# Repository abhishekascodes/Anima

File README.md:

# ANIMA: Interactive Tabletop Rock-Paper-Scissors Robot

Hey! I am Abhishek, and this is **ANIMA**, an interactive humanoid tabletop robot designed to play Rock-Paper-Scissors with people in real time. I am building this project for **Hack Club Fallen** with the goal of bringing it to showcase at **Maker Faire Shenzhen 2026**.

---

## The Backstory (Or how I almost built an uncontrollable monster)

When I first started this project, I went down a crazy rabbit hole trying to build a 51-axis radial sphere organism. I thought having 48 micro servos wiggling in a giant ball would look incredible. 

It did not. 

Once I actually modeled it and ran the mechanical load numbers, reality hit me pretty hard:
1. **The power draw was absurd:** 48 servos running under load would pull upwards of 50 to 60 amps at stall. Trying to route that through moving joints is an easy way to start an electrical fire on a table.
2. **The physics did not work:** The moment arms on the radial links put massive cantilever bending torque right onto tiny plastic servo splines. They would have stripped in ten minutes.
3. **It was not fun to interact with:** At the end of the day, it was just a mechanical ball wiggling on a pole. People at a booth would look at it for five seconds and walk away.

So I scrapped the entire thing and pivoted to something I actually care about: a robot with personality that people can walk up to, play against, and laugh with. That is where ANIMA was born.

---

## Why Rock-Paper-Scissors? (And the Anti-Cheat Problem)

Almost every Rock-Paper-Scissors robot you see on YouTube or in research labs has a dirty secret: **it cheats**. 

They mount a 120 FPS high-speed camera pointed at your hand, run a lightweight computer vision model that detects the first 20 milliseconds of your fingers unfolding, and snap their winning move right before you finish throwing. You feel like the robot has superhuman reflexes, but really it is just waiting for you to commit and picking the counter.

I wanted ANIMA to play like a real human, with genuine stakes and proof that it is not looking at your hand:

* **Pre-Commitment:** Before the countdown even starts, the host computer picks its move randomly, hashes it with a 24-byte secret key using SHA-256, and splashes the hash across the big screen.
* **Physical Blackout:** While the countdown is running, a micro servo swings a physical, opaque blackout shutter blade over the camera lens. The robot literally cannot see you.
* **Instant Mechanical Throw:** On the final beat, high-speed electromagnetic solenoids yank Kevlar tendons to snap the fingers into Rock, Paper, or Scissors in under 15 milliseconds.
* **Cryptographic Reveal:** Digital Hall effect sensors at the finger stops verify that the hand physically reached the pose. Only after the physical throw is locked does the camera shutter swing open, the secret key get published, and the winner get called. Anyone watching can verify the hash matches the pre-countdown commitment.

---

## Visual Showcase

| Hero Striker Angle | Expressive Portrait View |
| :---: | :---: |
|  |  |

| Internal Cutaway & Tendon Routing | High-Speed Playing Hand |
| :---: | :---: |
|  |  |

| Custom 4-Layer Controller (KiCad 10) | Multi-Sheet Schematic |
| :---: | :---: |
|  |  |

---

## How It Works Under the Hood

### 1. Mechanics and 3D Printed Parts
I split the 3D design into two layers:
* **The structural skeleton (`cad/Parts/` and `ANIMA_RPS_Upper_Torso.FCStd`):** Modeled with exact engineering tolerances in FreeCAD and CadQuery. Every joint that experiences side loads (like the neck pan and striker arm) rides on 688ZZ radial ball bearings so the motor shafts never take bending stress. Brass M3 heat-set inserts are melted into every mounting boss so you can disassemble and rebuild it without stripping plastic threads.
* **The sculpted outer shell (`cad/ANIMA Studio.blend` and `.glb`):** Modeled in Blender to give ANIMA a friendly, retro-futuristic aesthetic. The outer shells cover all the ugly wire harnesses while leaving airflow ducts for the heatsinks and solenoids.

For the fingers, standard servos were way too slow (they take 100 to 200 ms to rotate 60 degrees). Instead, I used **12V pull solenoids** attached to braided 100 lb Dyneema/Kevlar lines running through low-friction PTFE guide tubes. When a coil fires, the fingers snap shut in about 12 to 15 ms, fast enough to match human reflex speed.

### 2. Custom 4-Layer PCB (`ANIMA_RPS_Controller`)
You cannot run high-current inductive solenoids off breadboards or standard hobby shields without crashing your microcontroller. Every time a solenoid coil turns off, the collapsing magnetic field throws a massive negative voltage spike that resets the CPU.

To solve this, I designed a dedicated 4-layer PCB in KiCad 10:
* **Brain:** ESP32-S3-WROOM-1 module running hardware PWM timers and fast GPIO pin-change interrupts for the Hall effect limit sensors.
* **Power Isolation:** The 3.3V digital logic has its own ground plane and is powered through an onboard AP63203 buck converter. The 12V coil rail is completely separated, driven by fast UCC27517 gate drivers, IRLZ44N power MOSFETs, SS54 Schottky catch diodes, and SMBJ24A TVS diodes to soak up inductive kickback.
* **Safety Hardware:** A physical emergency stop button runs straight into an onboard SN74LVC1G00 hardware logic gate. If someone hits the E-stop, the power to all coils and servos is killed in hardware immediately, even if the microcontroller firmware locks up.
* **Audio & Presence:** An onboard MAX98357A I2S Class-D amplifier drives an internal speaker for voice lines and sound effects, and an LD2410 24 GHz mmWave radar header detects when someone walks up to the booth.

### 3. Firmware and Software Architecture
* **ESP32-S3 Firmware (`firmware/esp32/`):** Written in C++ using PlatformIO. Uses high-resolution hardware timers (LEDC) to command servos with zero jitter. When a move is triggered, it pulses the solenoid MOSFETs with an initial 100% kick for 25 ms to overcome mechanical inertia, then drops to a 30% PWM hold current so the coils do not overheat.
* **Host Vision & Game Engine (`firmware/pi/`):** Runs on a Raspberry Pi 5. It handles MediaPipe hand tracking for visitor gesture recognition, manages game state, drives the HDMI commitment display, and communicates with the ESP32 over high-speed USB-serial at 921,600 baud.

---

## Repository Tour

Here is what you will find in this repo:

```
├── cad/
│   ├── README.md                     # Joint angles, mechanical specs and print settings
│   ├── ANIMA Studio.blend            # Master Blender model for outer shells and renders
│   ├── ANIMA Studio.glb              # 3D web asset you can view in your browser
│   ├── ANIMA Studio Fairing Envelopes.step # Clean exterior CAD surfaces
│   ├── ANIMA_RPS_Upper_Torso.FCStd   # Parametric FreeCAD assembly
│   ├── ANIMA_RPS_Upper_Torso.step    # Full structural assembly STEP
│   ├── anima_rps_assembly.py         # Python CadQuery script generating the skeleton
│   └── Parts/                        # All 41 individual 3D printable leaf parts
├── electronics/
│   ├── ANIMA_RPS_Controller.kicad_sch # Complete 8-sheet KiCad schematic (0 ERC errors)
│   ├── ANIMA_RPS_Controller.kicad_pcb # Routed 4-layer PCB layout (0 DRC errors)
│   ├── gerbers.zip                   # Ready-to-order fab package for JLCPCB / PCBWay
│   └── PCB_BOM.csv                   # Part numbers and footprints for all 47 components
├── firmware/
│   ├── esp32/                        # PlatformIO C++ firmware with hardware timers
│   └── pi/                           # Python host scripts and FAIR anti-cheat demo
├── docs/
│   ├── FAIR_PROTOCOL.md              # Deep dive into the SHA-256 anti-cheat protocol
│   ├── INTEGRATION.md                # Wiring harnesses, connectors and pinouts
│   └── images/                       # PCB renders, CAD cutaways and showcase shots
├── bom.csv                           # Full itemized grant BOM in USD ($757.20)
└── README.md
```

---

## Current Status & Next Steps

* [x] Complete mechanical overhaul from radial monster to tabletop humanoid
* [x] Design 41 structural parts in FreeCAD with 688ZZ bearing supports
* [x] Sculpt exterior aesthetic shells in Blender and export STEP envelopes
* [x] Design custom 4-layer PCB in KiCad 10 (ERC: 0 errors, DRC: 0 errors)
* [x] Generate production Gerbers and fitted component BOM
* [x] Write ESP32-S3 firmware with solenoid kick/hold logic
* [x] Write Python FAIR protocol benchmark and camera shutter lock script
* [ ] 3D print structural frame in PETG (0.2mm layer height, 4 walls)
* [ ] Order custom PCB and solder surface mount parts
* [ ] Assemble tendon hand and bench-test 15ms reaction times
* [ ] Pack it all up and take it to Shenzhen!

---

Built with a lot of coffee and late nights by Abhishek A S for Hack Club Fallen.

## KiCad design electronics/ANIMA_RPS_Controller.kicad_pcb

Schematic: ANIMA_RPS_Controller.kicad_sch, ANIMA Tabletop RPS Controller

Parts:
C1: 1uF; C_0603_1608Metric
C2, C4, C8, C10, C11, C12, C14, C15, C16: 100nF; C_0603_1608Metric
C3: 22uF; C_1206_3216Metric
C5: 10uF 16V; C_1206_3216Metric
C6, C7: 22uF 10V; C_1206_3216Metric
C13, C17: 10uF; C_0805_2012Metric
C18: 470uF 25V; CP_Radial_D8.0mm_P3.50mm
C19: 100nF 50V; C_0805_2012Metric
C20, C21, C22: 1uF; C_0805_2012Metric
D1, D2, D3: SS54-E3/57T; D_SMC
D4, D5, D6: SMBJ24A-E3/52; D_SMB
H1, H2, H3, H4: M3 Mount; MountingHole_3.2mm_M3
J1: 5V LOGIC IN; TerminalBlock_Phoenix_MKDS-3-2-5.08_1x02_P5.08mm_Horizontal
J2: PI UART; JST_XH_B3B-XH-A_1x03_P2.50mm_Vertical
J3: PROGRAM UART; JST_XH_B5B-XH-A_1x05_P2.50mm_Vertical
J5: STOP AUX CONTACT; JST_XH_B2B-XH-A_1x02_P2.50mm_Vertical
J6: HALL HARNESS; JST_XH_B9B-XH-A_1x09_P2.50mm_Vertical
J7: COIL 1 NTC; JST_XH_B2B-XH-A_1x02_P2.50mm_Vertical
J8: COIL 2 NTC; JST_XH_B2B-XH-A_1x02_P2.50mm_Vertical
J9: COIL 3 NTC; JST_XH_B2B-XH-A_1x02_P2.50mm_Vertical
J10: MODE START REMATCH; JST_XH_B4B-XH-A_1x04_P2.50mm_Vertical
J11: LD2410 RADAR; JST_XH_B4B-XH-A_1x04_P2.50mm_Vertical
J12: PAN_SERVO; JST_XH_B2B-XH-A_1x02_P2.50mm_Vertical
J13: TILT_SERVO; JST_XH_B2B-XH-A_1x02_P2.50mm_Vertical
J14: ELBOW_SERVO; JST_XH_B2B-XH-A_1x02_P2.50mm_Vertical
J15: JAW_SERVO; JST_XH_B2B-XH-A_1x02_P2.50mm_Vertical
J16: SHUTTER_SERVO; JST_XH_B2B-XH-A_1x02_P2.50mm_Vertical
J17: PIXELS SIGNAL; JST_XH_B2B-XH-A_1x02_P2.50mm_Vertical
J18: SPEAKER BTL; JST_XH_B2B-XH-A_1x02_P2.50mm_Vertical
J19: 12V COIL CUT INPUT; TerminalBlock_Phoenix_MKDS-3-2-5.08_1x02_P5.08mm_Horizontal
J20: COIL 1; TerminalBlock_Phoenix_MKDS-3-2-5.08_1x02_P5.08mm_Horizontal
J21: COIL 2; TerminalBlock_Phoenix_MKDS-3-2-5.08_1x02_P5.08mm_Horizontal
J22: COIL 3; TerminalBlock_Phoenix_MKDS-3-2-5.08_1x02_P5.08mm_Horizontal
L1: 4.7uH SRP5030TA-4R7M; L_Bourns_SRP5030T
Q1, Q2, Q3: IRLZ44NPBF; TO-220-3_Vertical
R1, R2, R3, R10, R11, R12, R13, R14, R15, R16, R20, R21, R22, R37, R38, R39: 10k; R_0603_1608Metric
R4, R23, R24, R25, R26, R27, R29, R31, R32, R33: 100k; R_0603_1608Metric
R17, R18, R19: 10k 1%; R_0603_1608Metric
R28: 330R; R_0603_1608Metric
R30: 0R; R_0603_1608Metric
R34, R35, R36: 22R; R_0603_1608Metric
U1: ESP32-S3-WROOM-1-N8; ESP32-S3-WROOM-1_Edge
U2: AP63203WU-7; TSOT-23-6
U3: SN74LVC1G00DBVR; SOT-23-5
U4: SN74AHCT244PWR; TSSOP-20_4.4x6.5mm_P0.65mm
U5: SN74AHCT1G125DBVR; SOT-23-5
U6: MAX98357AETE+T; TQFN-16-1EP_3x3mm_P0.5mm_EP1.23x1.23mm
U7, U8, U9: UCC27517ADBVR; SOT-23-5

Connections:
/+3V3: C2.1, C3.1, C6.1, C7.1, C8.1, J5.1 (3V3), J6.1 (3V3), L1.2, R1.1, R2.1, R10.1, R11.1, R12.1, R13.1, R14.1, R15.1, R16.1, R17.1, R18.1, R19.1, R20.1, R21.1, R22.1, R30.1, U1.2 (3V3), U2.1 (FB), U3.5 (VCC)
/+5V_LOGIC: C5.1, C13.1, C14.1, C15.1, C16.1, C17.1, C20.1, C21.1, C22.1, J1.1 (5V), J11.1 (5V), U2.2 (EN), U2.3 (VIN), U4.20 (VCC), U5.5 (VCC), U6.7 (VDD), U6.8 (VDD), U7.1 (VDD), U8.1 (VDD), U9.1 (VDD)
/+12V_COIL_CUT: C18.1, C19.1, D1.1 (K), D2.1 (K), D3.1 (K), J19.1 (12V CUT), J20.1 (12V), J21.1 (12V), J22.1 (12V)
/AMP_SD: R30.2, U6.4 (SD_MODE)
/ARM_REQ: R4.1, U1.31 (IO38), U3.1 (A)
/AUDIO_BCLK: U1.32 (IO39), U6.16 (BCLK)
/AUDIO_DIN: U1.34 (IO41), U6.1 (DIN)
/AUDIO_LRCLK: U1.33 (IO40), U6.14 (LRCLK)
/BOOT_N: J3.5 (BOOT), R2.2, U1.27 (IO0)
/BUCK_BST: C4.1, U2.6 (BST)
/BUCK_SW: C4.2, L1.1, U2.5 (SW)
/COIL_1_D: D1.2 (A), D4.1 (K), J20.2 (SW RETURN), Q1.2 (D)
/COIL_2_D: D2.2 (A), D5.1 (K), J21.2 (SW RETURN), Q2.2 (D)
/COIL_3_D: D3.2 (A), D6.1 (K), J22.2 (SW RETURN), Q3.2 (D)
/COIL_PWM_1: R31.1, U1.4 (IO4), U7.3 (IN+)
/COIL_PWM_2: R32.1, U1.5 (IO5), U8.3 (IN+)
/COIL_PWM_3: R33.1, U1.6 (IO6), U9.3 (IN+)
/DRIVE_1: R34.1, U7.5 (OUT)
/DRIVE_2: R35.1, U8.5 (OUT)
/DRIVE_3: R36.1, U9.5 (OUT)
/ELBOW_PWM: R25.1, U1.9 (IO16), U4.6 (1A3)
/ELBOW_SERVO: J14.1 (PWM), U4.14 (1Y3)
/EN: C1.1, J3.4 (EN), R1.2, U1.3 (EN)
/ESTOP_OK: J5.2 (ESTOP_OK), R3.1, U1.13 (USB_D-), U3.2 (B)
/GATE_1: Q1.1 (G), R34.2, R37.1
/GATE_2: Q2.1 (G), R35.2, R38.1
/GATE_3: Q3.1 (G), R36.2, R39.1
/GND: C1.2, C2.2, C3.2, C5.2, C6.2, C7.2, C8.2, C10.2, C11.2, C12.2, C13.2, C14.2, C15.2, C16.2, C17.2, C18.2, C19.2, C20.2, C21.2, C22.2, D4.2 (A), D5.2 (A), D6.2 (A), J1.2 (GND), J2.1 (GND), J3.1 (GND), J6.2 (GND), J7.2 (GND), J8.2 (GND), J9.2 (GND), J10.1 (GND), J11.2 (GND), J12.2 (GND), J13.2 (GND), J14.2 (GND), J15.2 (GND), J16.2 (GND), J17.2 (GND), J19.2 (GND), Q1.3 (S), Q2.3 (S), Q3.3 (S), R3.2, R4.2, R23.2, R24.2, R25.2, R26.2, R27.2, R29.2, R31.2, R32.2, R33.2, R37.2, R38.2, R39.2, U1.1 (GND), U1.40 (GND), U1.41 (EP), U2.4 (GND), U3.3 (GND), U4.10 (GND), U4.13 (2A2), U4.15 (2A3), U4.17 (2A4), U5.1 (OE_N), U5.3 (GND), U6.3 (GND), U6.11 (GND), U6.15 (GND), U6.17 (EP), U7.2 (GND), U8.2 (GND), U9.2 (GND)
/H1_EXT: J6.3 (EXT 1), R10.2, U1.18 (IO10)
/H1_RET: J6.4 (RET 1), R11.2, U1.19 (IO11)
/H2_EXT: J6.5 (EXT 2), R12.2, U1.20 (IO12)
/H2_RET: J6.6 (RET 2), R13.2, U1.21 (IO13)
/H3_EXT: J6.7 (EXT 3), R14.2, U1.22 (IO14)
/H3_RET: J6.8 (RET 3), R15.2, U1.23 (IO21)
/JAW_PWM: R26.1, U1.10 (IO17), U4.8 (1A4)
/JAW_SERVO: J15.1 (PWM), U4.12 (1Y4)
/MCU_RX: J2.2 (HOST TX), J3.2 (ADAPTER TX), U1.36 (RXD0)
/MCU_TX: J2.3 (HOST RX), J3.3 (ADAPTER RX), U1.37 (TXD0)
/MODE_N: J10.2 (FAIR CONTACT), R20.2, U1.28 (IO35)
/NTC1_ADC: C10.1, J7.1 (SENSE), R17.2, U1.17 (IO9)
/NTC2_ADC: C11.1, J8.1 (SENSE), R18.2, U1.12 (IO8)
/NTC3_ADC: C12.1, J9.1 (SENSE), R19.2, U1.39 (IO1)
/PAN_PWM: R23.1, U1.7 (IO7), U4.2 (1A1)
/PAN_SERVO: J12.1 (PWM), U4.18 (1Y1)
/PIXEL_3V3: R29.1, U1.35 (IO42), U5.2 (A)
/PIXEL_BUF: R28.1, U5.4 (Y)
/PIXEL_DATA: J17.1 (DATA), R28.2
/RADAR_RX: J11.4 (RADAR TX), U1.25 (IO48)
/RADAR_TX: J11.3 (RADAR RX), U1.24 (IO47)
/REMATCH_N: J10.4 (REMATCH), R22.2, U1.30 (IO37)
/RUN_N: U3.4 (Y), U4.1 (OE1_N), U4.19 (OE2_N), U7.4 (IN-), U8.4 (IN-), U9.4 (IN-)
/SHUTTER_CLOSED: J6.9 (SHUTTER CLOSED), R16.2, U1.38 (IO2)
/SHUTTER_PWM: R27.1, U1.11 (IO18), U4.11 (2A1)
/SHUTTER_SERVO: J16.1 (PWM), U4.9 (2Y1)
/SPK_N: J18.2 (SPK-), U6.10 (OUTN)
/SPK_P: J18.1 (SPK+), U6.9 (OUTP)
/START_N: J10.3 (START), R21.2, U1.29 (IO36)
/TILT_PWM: R24.1, U1.8 (IO15), U4.4 (1A2)
/TILT_SERVO: J13.1 (PWM), U4.16 (1Y2)

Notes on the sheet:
ANIMA / UPPER-TORSO RPS CONTROLLER
ANIMA Tabletop RPS Controller v1.2 | Low-Voltage DC | ESP32-S3 + 5 Servos + 3 Coils + 7 Hall Stops | Abhishek A S
01 MCU AND RESET
Pi host UART 3.3 V only. Disconnect Pi UART when using the programming header.
UART0: cross TX/RX. EN and BOOT pull-ups on board.
IO19 senses the interlock. Native USB D-/D+ are unavailable.
02 LOGIC POWER
J1 receives regulated always-on 5 V DC. Pixel power uses its own external fused 5 V feed.
FB senses 3V3 after L1. Check regulator thermal and switching layout in review.
The Pi has independent 27 W power. Reference grounds are common at the DC star.
03 HARDWARE ARM INHIBIT
A maintained external DC disconnect interrupts coil and servo motor power.
Aux contact closes in healthy state. Missing contact or ARM_REQ low holds RUN_N high.
J5 carries logic only. The external DC disconnect interrupts motor power independently.
Controller starts disarmed and must receive a deliberate reset after a stop.
04 SENSOR HARNESS
Seven open-drain stops at 3.3 V. Thermistors are board-excited dividers.
Use 10 kOhm NTCs with known Beta. Treat open or short circuits as faults.
Each DRV5033 gets local bypass at its remote sensor. Pair signal with ground throughout.
05 VISITOR CONTROLS AND PRESENCE
All contact inputs are normally open to ground.
Check the exact LD2410 variant and its 3.3 V UART levels at the harness.
06 FIVE SERVO SIGNALS
Signal headers carry PWM and return only. Motor power reaches servos through the separate fused 6 V loom.
OE is hardware-inhibited. TTL inputs and 5 V logic outputs suit the PWM loom.
07 CHEST, EYES AND AUDIO
The external pixel supply must be current-limited to its verified panel draw.
Bridge output: floating speaker pair, neither lead connects to ground. Keep the pair short.
Send the same mono sample on both audio channels. GAIN is intentionally open.
08 FUSED 12 V COILS
Input is downstream of the external DC cutoff. Do not drive coils until an actual pulse/thermal profile is validated.
Channel 1 index + middle | Channel 2 ring + little | Channel 3 thumb
Clamp diode is across each coil output. TVS catches drain overshoot. Confirm clamp energy and release on the bench.
Do not route servo motor current through this board. Confirm peak-rail current, copper thermal rise and cutoff behavior.

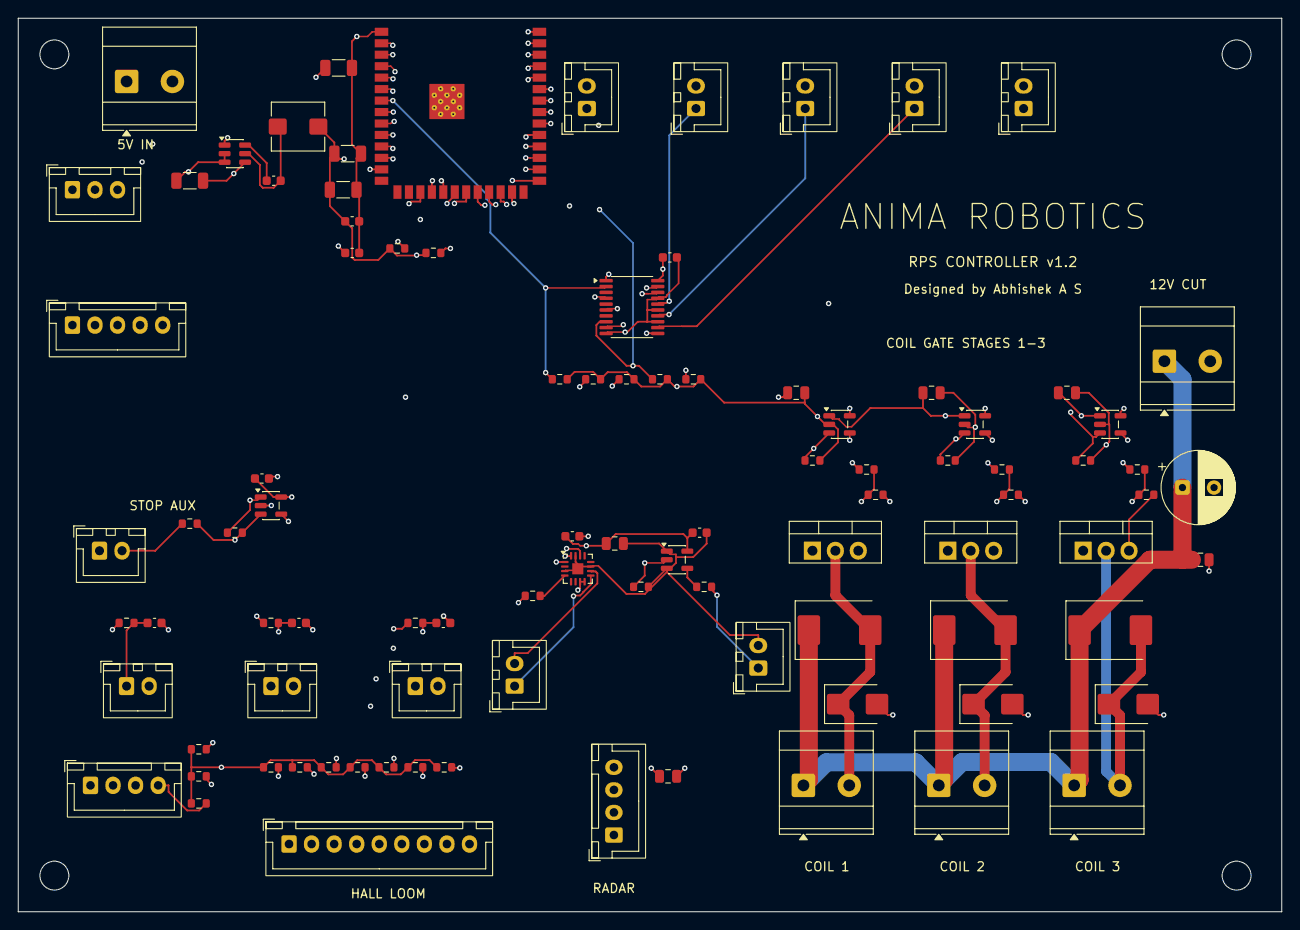
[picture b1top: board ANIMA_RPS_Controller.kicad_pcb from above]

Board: 4 copper layers, 140.0 x 99.0 mm, 99 parts (0 on the bottom side), 59 nets.

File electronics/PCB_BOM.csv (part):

"Group","Part","Specification","Installed quantity","Unit INR","Extended INR","Supplier","Purchase link","Ownership","Price basis","Release gate","Installed role","PCB references"
"PCB fitted","ESP32-S3-WROOM-1-N8","ANIMA_Footprints:ESP32-S3-WROOM-1_Edge","1",,,"DigiKey India","https://www.digikey.in/en/products?keywords=ESP32-S3-WROOM-1-N8","Included in the assembled PCB allowance","Exact part or footprint-matched catalog lookup","Assembler must resolve exact part, ratings and availability","ESP32-S3-WROOM-1-N8","U1"
"PCB fitted","resistor 10k 0603","Resistor_SMD:R_0603_1608Metric","16",,,"DigiKey India","https://www.digikey.in/en/products?keywords=resistor%2010k%200603","Included in the assembled PCB allowance","Exact part or footprint-matched catalog lookup","Assembler must resolve exact part, ratings and availability","10k","R1 R2 R3 R10 R11 R12 R13 R14 R15 R16 R20 R21 R22 R37 R38 R39"
"PCB fitted","capacitor 1uF 0603","Capacitor_SMD:C_0603_1608Metric","1",,,"DigiKey India","https://www.digikey.in/en/products?keywords=capacitor%201uF%200603","Included in the assembled PCB allowance","Exact part or footprint-matched catalog lookup","Assembler must resolve exact part, ratings and availability","1uF","C1"
"PCB fitted","capacitor 100nF 0603","Capacitor_SMD:C_0603_1608Metric","9",,,"DigiKey India","https://www.digikey.in/en/products?keywords=capacitor%20100n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","Included in the assembled PCB allowance","Exact part or footprint-matched catalog lookup","Assembler must resolve exact part, ratings and availability","100nF","C2 C4 C8 C10 C11 C12 C14 C15 C16"
"PCB fitted","capacitor 22uF 1206","Capacitor_SMD:C_1206_3216Metric","1",,,"DigiKey India","https://www.digikey.in/en/products?keywords=capacitor%2022uF%201206","Included in the assembled PCB allowance","Exact part or footprint-matched catalog lookup","Assembler must resolve exact part, ratings and availability","22uF","C3"
"PCB fitted","B3B-XH-A","Connector_JST:JST_XH_B3B-XH-A_1x03_P2.50mm_Vertical","1",,,"DigiKey India","https://www.digikey.in/en/products?keywords=B3B-XH-A","Included in the assembled PCB allowance","Exact part or footprint-matched catalog lookup","Assembler must resolve exact part, ratings and availability","PI UART","J2"
"PCB fitted","B5B-XH-A","Connector_JST:JST_XH_B5B-XH-A_1x05_P2.50mm_Vertical","1",,,"DigiKey India","https://www.digikey.in/en/products?keywords=B5B-XH-A","Included in the assembled PCB allowance","Exact part or footprint-matched catalog lookup","Assembler must resolve exact part, ratings and availability","PROGRAM UART","J3"
"PCB fitted","Phoenix Contact MKDS 3/2-5.08","TerminalBlock_Phoenix:TerminalBlock_Phoenix_MKDS-3-2-5.08_1x02_P5.08mm_Horizontal","1",,,"DigiKey India","https://www.digikey.in/en/products?keywords=Phoenix%20Contac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","Included in the assembled PCB allowance","Exact part or footprint-matched catalog lookup","Assembler must resolve exact part, ratings and availability","5V LOGIC IN","J1"
"PCB fitted","AP63203WU-7","Package_TO_SOT_SMD:TSOT-23-6","1",,,"DigiKey India","https://www.digikey.in/en/products?keywords=AP63203WU-7","Included in the assembled PCB allowance","Exact part or footprint-matched catalog lookup","Assembler must resolve exact part, ratings and availability","AP63203WU-7","U2"
"PCB fitted","4.7uH SRP5030TA-4R7M","Inductor_SMD:L_Bourns_SRP5030T","1",,,"DigiKey India","https://www.digikey.in/en/products?keywords=SRP5030TA-4R7M","Included in the assembled PCB allowance","Exact part or footprint-matched catalog lookup","Assembler must resolve exact part, ratings and availability","4.7uH SRP5030TA-4R7M","L1"
"PCB fitted","capacitor 10uF 16V 1206","Capacitor_SMD:C_1206_3216Metric","1",,,"DigiKey India","https://www.digikey.in/en/products?keywords=capacitor%2010uF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","Included in the assembled PCB allowance","Exact part or footprint-matched catalog lookup","Assembler must resolve exact part, ratings and availability","10uF 16V","C5"
"PCB fitted","capacitor 22uF 10V 1206","Capacitor_SMD:C_1206_3216Metric","2",,,"DigiKey India","https://www.digikey.in/en/products?keywords=capacitor%2022uF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","Included in the assembled PCB allowance","Exact part or footprint-matched catalog lookup","Assembler must resolve exact part, ratings and availability","22uF 10V","C6 C7"
"PCB fitted","B2B-XH-A","Connector_JST:JST_XH_B2B-XH-A_1x02_P2.50mm_Vertical","1",,,"DigiKey India","https://www.digikey.in/en/products?keywords=B2B-XH-A","Included in the assembled PCB allowance","Exact part or footprint-matched catalog lookup","Assembler must resolve exact part, ratings and availability","STOP AUX CONTACT","J5"
"PCB fitted","SN74LVC1G00DBVR","Package_TO_SOT_SMD:SOT-23-5","1",,,"DigiKey India","https://www.digikey.in/en/products?keywords=SN74LVC1G00DBVR","Included in the assembled PCB allowance","Exact part or footprint-matched catalog lookup","Assembler must resolve exact part, ratings and availability","SN74LVC1G00DBVR","U3"
"PCB fitted","resistor 100k 0603","Resistor_SMD:R_0603_1608Metric","10",,,"DigiKey India","https://www.digikey.in/en/products?keywords=resistor%20100k%200603","Included in the assembled PCB allowance","Exact part or footprint-matched catalog lookup","Assembler must resolve exact part, ratings and availability","100k","R4 R23 R24 R25 R26 R27 R29 R31 R32 R33"
"PCB fitted","B9B-XH-A","Connector_JST:JST_XH_B9B-XH-A_1x09_P2.50mm_Vertical","1",,,"DigiKey India","https://www.digikey.in/en/products?keywords=B9B-XH-A","Included in the assembled PCB allowance","Exact part or footprint-matched catalog lookup","Assembler must resolve exact part, ratings and availability","HALL HARNESS","J6"
"PCB fitted","B2B-XH-A","Connector_JST:JST_XH_B2B-XH-A_1x02_P2.50mm_Vertical","1",,,"DigiKey India","https://www.digikey.in/en/products?keywords=B2B-XH-A","Included in the assembled PCB allowance","Exact part or footprint-matched catalog lookup","Assembler must resolve exact part, ratings and availability","COIL 1 NTC","J7"
"PCB fitted","resistor 10k 1% 0603","Resistor_SMD:R_0603_1608Metric","3",,,"DigiKey India","https://www.digikey.in/en/products?keywords=resistor%2010k%2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","Included in the assembled PCB allowance","Exact part or footprint-matched catalog lookup","Assembler must resolve exact part, ratings and availability","10k 1%","R17 R18 R19"
"PCB fitted","B2B-XH-A","Connector_JST:JST_XH_B2B-XH-A_1x02_P2.50mm_Vertical","1",,,"DigiKey India","https://www.digikey.in/en/products?keywords=B2B-XH-A","Included in the assembled PCB allowance","Exact part or footprint-matched catalog lookup","Assembler must resolve exact part, ratings and availability","COIL 2 NTC","J8"
"PCB fitted","B2B-XH-A","Connector_JST:JST_XH_B2B-XH-A_1x02_P2.50mm_Vertical","1",,,"DigiKey India","https://www.digikey.in/en/products?keywords=B2B-XH-A","Included in the assembled PCB allowance","Exact part or footprint-matched catalog lookup","Assembler must resolve exact part, ratings and availability","COIL 3 NTC","J9"
"PCB fitted","B4B-XH-A","Connector_JST:JST_XH_B4B-XH-A_1x04_P2.50mm_Vertical","1",,,"DigiKey India","https://www.digikey.in/en/products?keywords=B4B-XH-A","Included in the assembled PCB allowance","Exact part or footprint-matched catalog lookup","Assembler must resolve exact part, ratings and availability","MODE START REMATCH","J10"
"PCB fitted","B4B-XH-A","Connector_JST:JST_XH_B4B-XH-A_1x04_P2.50mm_Vertical","1",,,"DigiKey India","https://www.digikey.in/en/products?keywords=B4B-XH-A","Included in the assembled PCB allowance","Exact part or footprint-matched catalog lookup","Assembler must resolve exact part, ratings and availability","LD2410 RADAR","J11"
"PCB fitted","capacitor 10uF 0805","Capacitor_SMD:C_0805_2012Metric","2",,,"DigiKey India","https://www.digikey.in/en/products?keywords=capacitor%2010uF%200805","Included in the assembled PCB allowance","Exact part or footprint-matched catalog lookup","Assembler must resolve exact part, ratings and availability","10uF","C13 C17"
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
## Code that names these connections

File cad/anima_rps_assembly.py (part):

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register('jaw_shell',panel([(-25,5),(25,5),(20,-6),(-20,-6)],10),'metal')
fit('jaw_shell',(0,29,455))
register('microservo_envelope',box(24,13,25),'frame','Provisional MG90S volume',True)
fit('microservo_envelope',(0,0,457),label='jaw_servo')

register('fixed_camera_arm',box(12,48,56),'metal')
fit('fixed_camera_arm',(132,26,402))
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aim_camera('camera_board_envelope',(-3,4,0))
aim_camera('camera_lens_envelope',(-3,6,0))
aim_camera('camera_shutter_blade',(18,14,10),clock=-32)
aim_camera('microservo_envelope',(21,-7,3),label='shutter_servo')

register('countdown_upper_link',panel([(-15,7),(15,7),(22,-98),(14,-117),(-14,-117),(-22,-99)],19),'metal')
fit('countdown_upper_link',(147,29,353),y_angle=-9)
fit('ds3225_envelope',(147,13,234),y_angle=90,label='elbow_servo')
register('countdown_forearm_shell',panel([(-20,4),(20,4),(26,-73),(15,-94),(-15,-94),(-25,-72)],20),'ivory')
fit('countdown_forearm_shell',(154,42,236),y_angle=-18)
register('countdown_striker_pad',box(35,38,14),'rubber')
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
